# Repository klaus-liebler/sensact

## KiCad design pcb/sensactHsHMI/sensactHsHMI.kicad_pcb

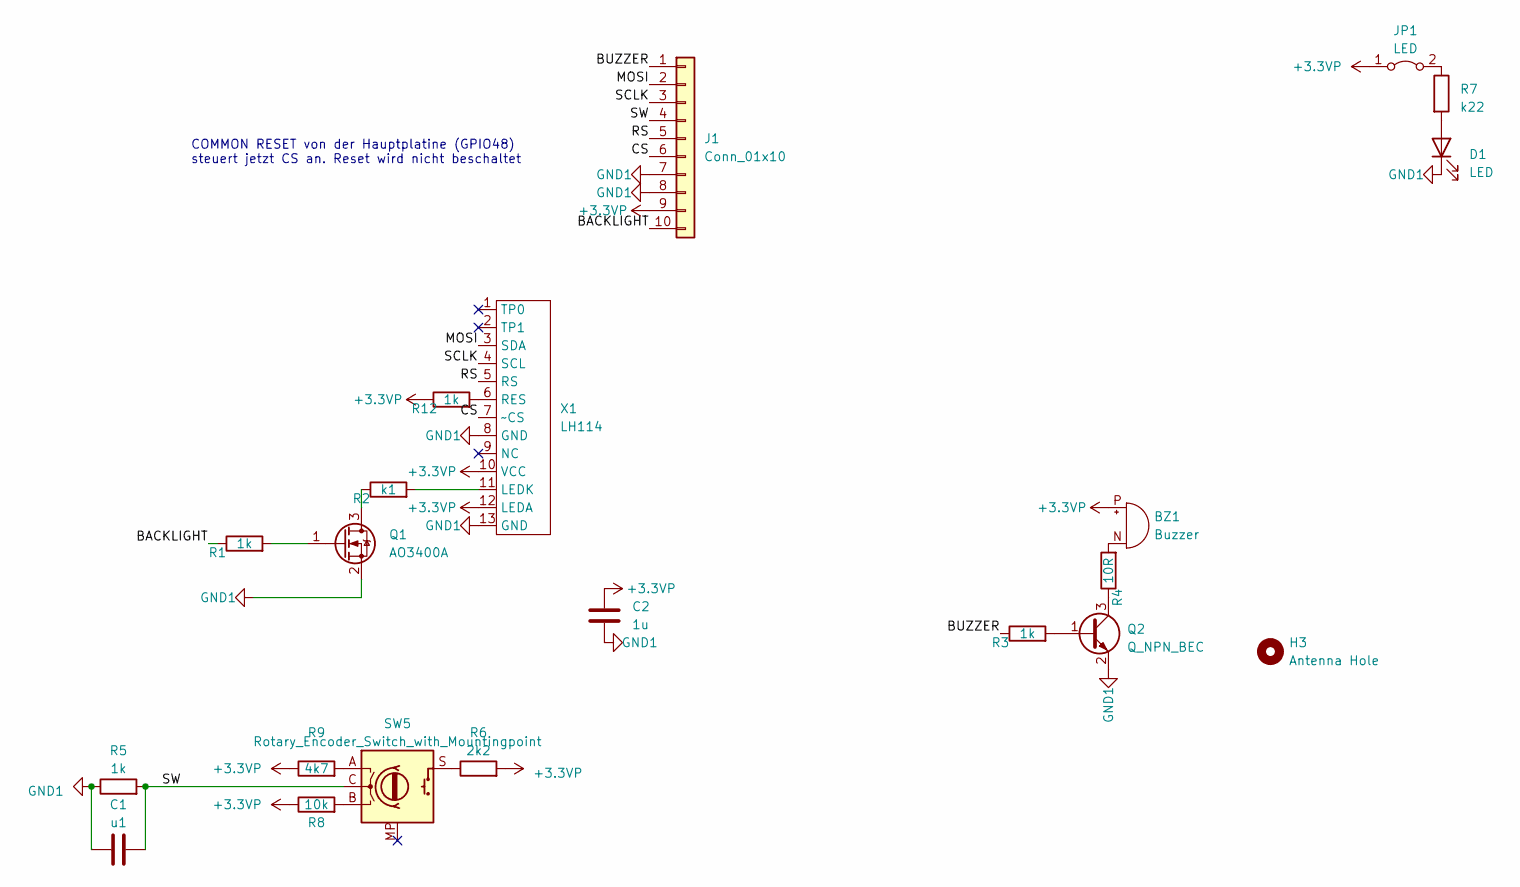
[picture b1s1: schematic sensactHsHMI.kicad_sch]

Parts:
BZ1: Buzzer; XDCR_CMT-7525-80-SMT-TR_handsolder
C1: u1; C_0805_2012Metric_Pad1.18x1.45mm_HandSolder
C2: 1u; C_0805_2012Metric_Pad1.18x1.45mm_HandSolder
D1: LED; LED_PLCC_2835_Handsoldering
H3: Antenna Hole; SMA_Schraubbefestigung
J1: Conn_01x10; FFC_FPC_10_P0.50mm_Horizontal
JP1: LED; SolderJumper-2_P1.3mm_Bridged_RoundedPad1.0x1.5mm
Q1: AO3400A; SOT-23_Handsoldering
Q2: Q_NPN_BEC; SOT-23_Handsoldering
R1, R3, R5, R12: 1k; R_0805_2012Metric_Pad1.20x1.40mm_HandSolder
R2: k1; R_0805_2012Metric_Pad1.20x1.40mm_HandSolder
R4: 10R; R_0805_2012Metric_Pad1.20x1.40mm_HandSolder
R6: 2k2; R_0805_2012Metric_Pad1.20x1.40mm_HandSolder
R7: k22; R_1206_3216Metric_Pad1.30x1.75mm_HandSolder
R8: 10k; R_0805_2012Metric_Pad1.20x1.40mm_HandSolder
R9: 4k7; R_0805_2012Metric_Pad1.20x1.40mm_HandSolder
SW5: Rotary_Encoder_Switch_with_Mountingpoint; Mitsumi_SIQ-02FVS3
X1: LH114; FP-114 13pol top only

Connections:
+3.3VP: BZ1.P (-), C2.1, J1.9, JP1.1 (A), R6.2, R8.1, R9.1, R12.1, X1.10 (VCC), X1.12 (LEDA)
/BACKLIGHT: J1.10, R1.1
/BUZZER: J1.1, R3.1
/CS: J1.6, X1.7 (~CS)
/MOSI: J1.2, X1.3 (SDA)
/RS: J1.5, X1.5 (RS)
/SCLK: J1.3, X1.4 (SCL)
/SW: C1.2, J1.4, R5.2, SW5.C
GND1: C1.1, C2.2, D1.1 (K), J1.7, J1.8, Q1.2 (S), Q2.2 (E), R5.1, X1.8 (GND), X1.13 (GND)
unnamed: BZ1.N (+), R4.2
unnamed: D1.2 (A), R7.2
unnamed: JP1.2 (B), R7.1
unnamed: Q1.3 (D), R2.1
unnamed: Q1.1 (G), R1.2
unnamed: Q2.1 (B), R3.2
unnamed: Q2.3 (C), R4.1
unnamed: R6.1, SW5.S
unnamed: R8.2, SW5.B
unnamed: R9.2, SW5.A
unnamed: R2.2, X1.11 (LEDK)
unnamed: R12.2, X1.6 (RES)

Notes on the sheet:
COMMON RESET von der Hauptplatine (GPIO48) steuert jetzt CS an. Reset wird nicht beschaltet

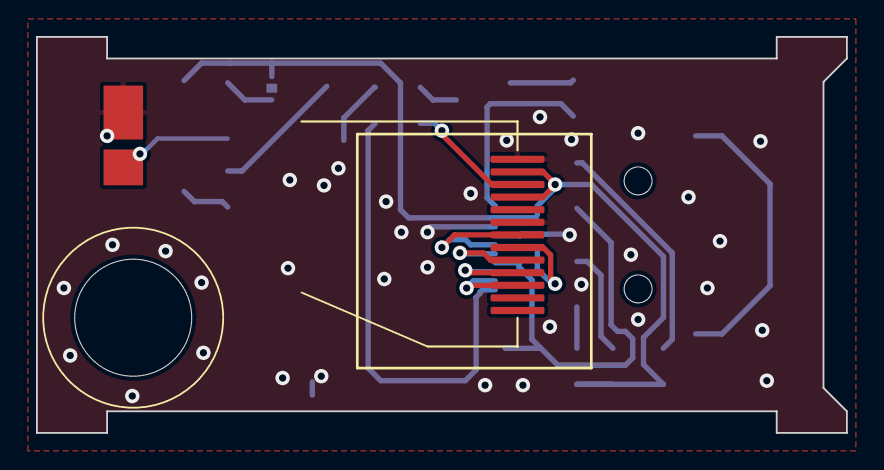
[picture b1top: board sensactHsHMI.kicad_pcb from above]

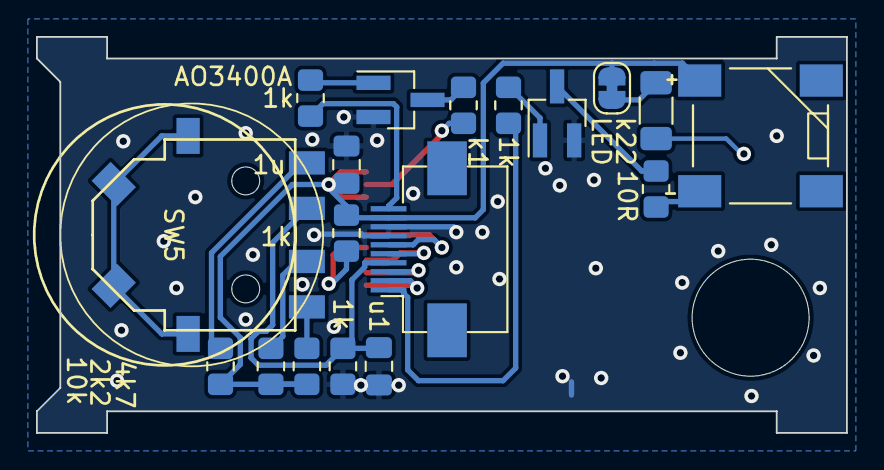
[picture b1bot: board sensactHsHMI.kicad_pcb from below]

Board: 2 copper layers, 45.0 x 22.0 mm, 21 parts (18 on the bottom side), 21 nets.

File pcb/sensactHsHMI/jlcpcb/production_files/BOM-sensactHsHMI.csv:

Comment,Designator,Footprint,LCSC
LH114,X1,FP-114 13pol top only,
u1,C1,C_0805_2012Metric_Pad1.18x1.45mm_HandSolder,
10R,R4,R_0805_2012Metric_Pad1.20x1.40mm_HandSolder,
1k,R3,R_0805_2012Metric_Pad1.20x1.40mm_HandSolder,
2k2,R6,R_0805_2012Metric_Pad1.20x1.40mm_HandSolder,
Buzzer,BZ1,XDCR_CMT-7525-80-SMT-TR_handsolder,
k1,R2,R_0805_2012Metric_Pad1.20x1.40mm_HandSolder,
1k,R1,R_0805_2012Metric_Pad1.20x1.40mm_HandSolder,
Conn_01x10,J1,FFC_FPC_10_P0.50mm_Horizontal,
Q_NPN_BEC,Q2,SOT-23_Handsoldering,
10k,R8,R_0805_2012Metric_Pad1.20x1.40mm_HandSolder,
1k,R5,R_0805_2012Metric_Pad1.20x1.40mm_HandSolder,
k22,R7,R_1206_3216Metric_Pad1.30x1.75mm_HandSolder,
LED,D1,LED_PLCC_2835_Handsoldering,
Antenna Hole,H3,SMA_Schraubbefestigung,
1u,C2,C_0805_2012Metric_Pad1.18x1.45mm_HandSolder,
1k,R12,R_0805_2012Metric_Pad1.20x1.40mm_HandSolder,
4k7,R9,R_0805_2012Metric_Pad1.20x1.40mm_HandSolder,
Rotary_Encoder_Switch_with_Mountingpoint,SW5,Mitsumi_SIQ-02FVS3,
LED,JP1,SolderJumper-2_P1.3mm_Bridged_RoundedPad1.0x1.5mm,

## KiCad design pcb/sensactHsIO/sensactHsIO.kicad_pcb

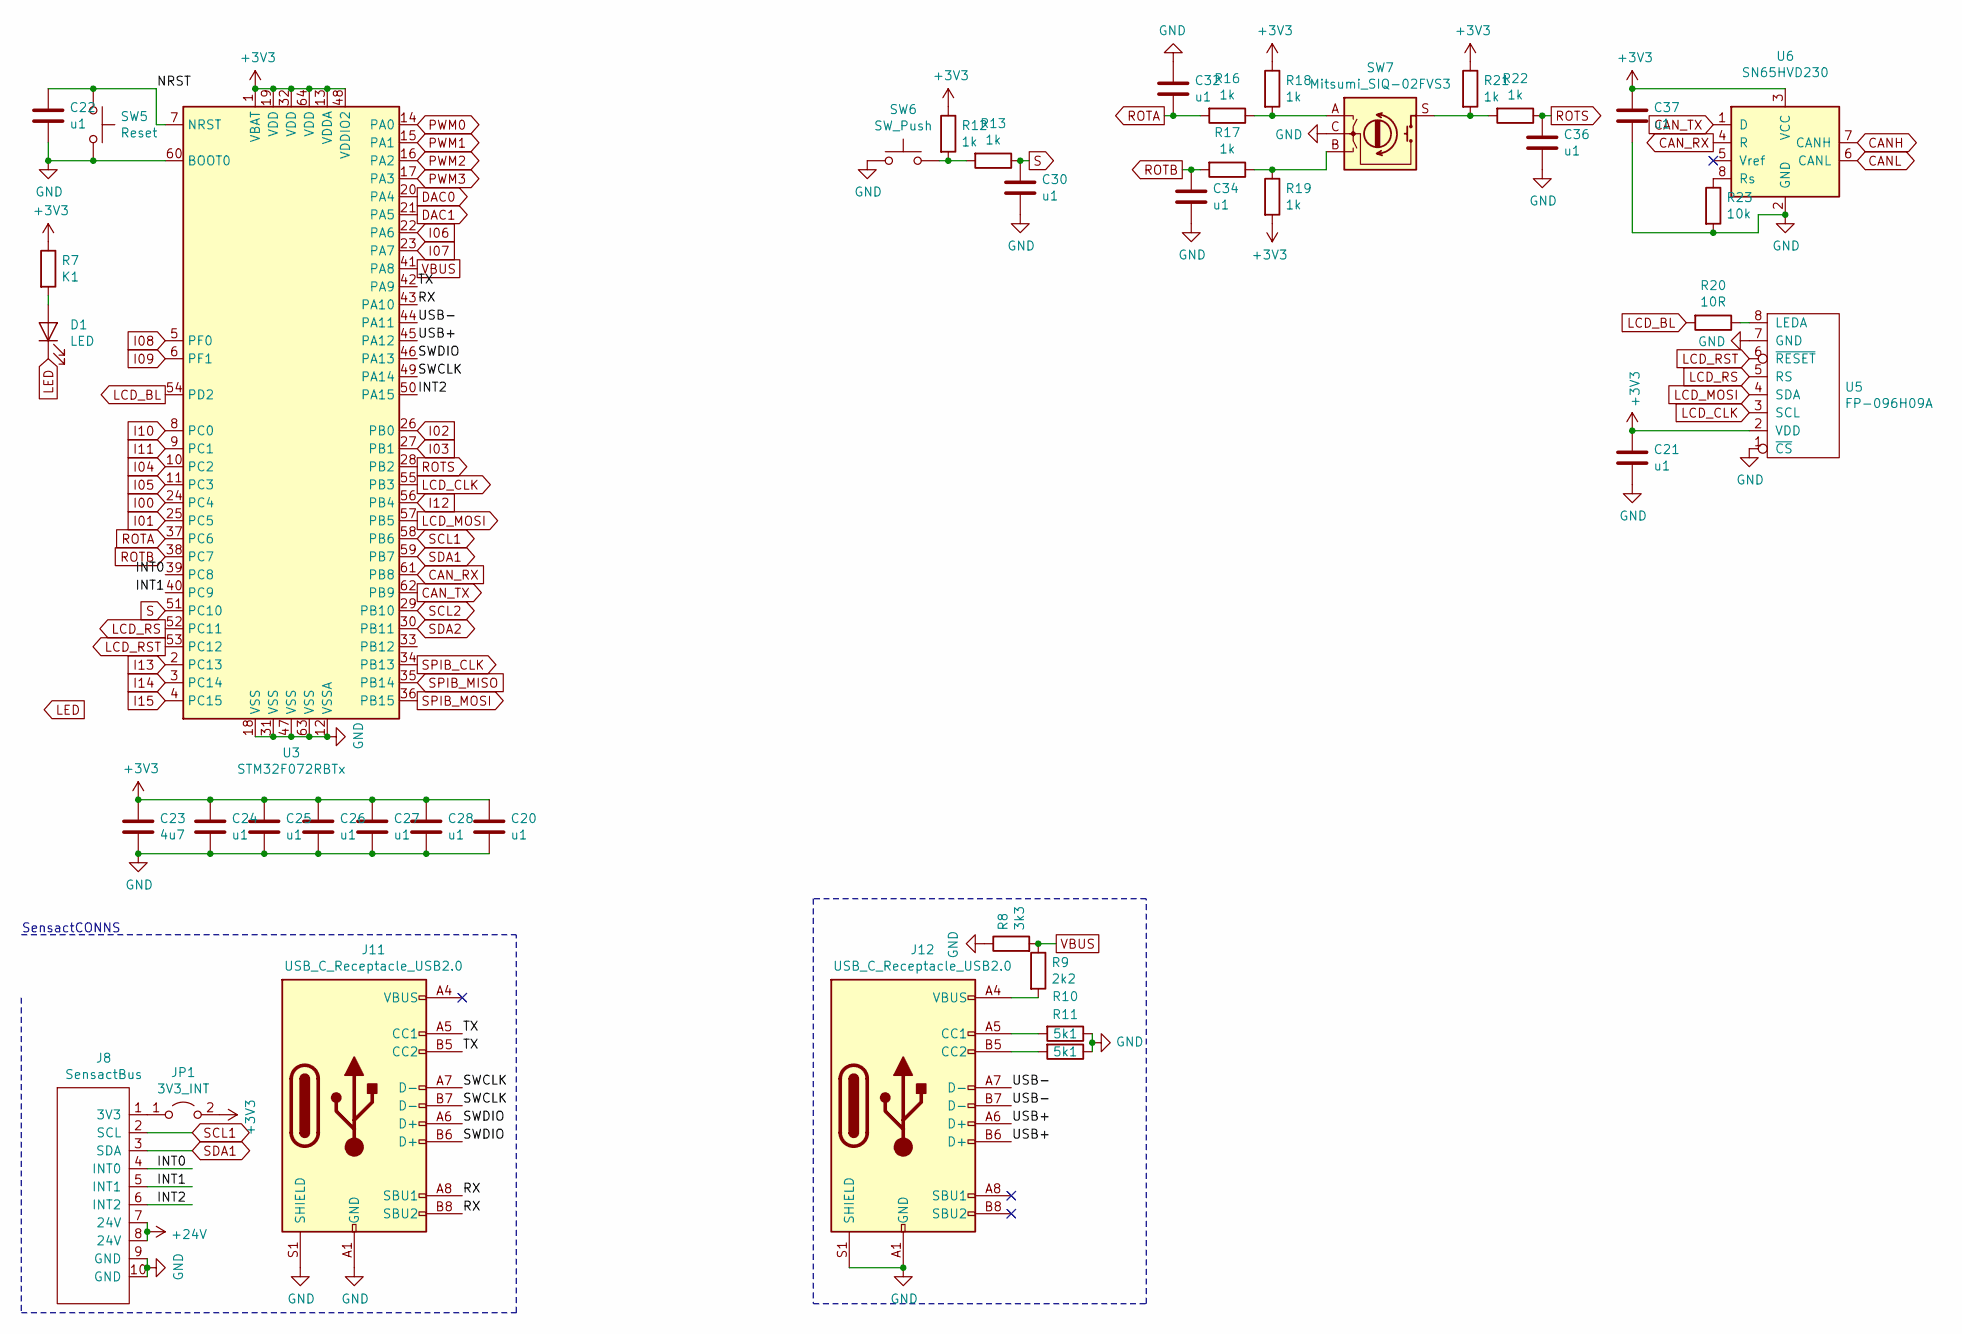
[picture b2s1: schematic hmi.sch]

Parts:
C20, C21, C22, C24, C25, C26, C27, C28, C30, C32, C34, C36, C37: u1; C_0805_2012Metric_Pad1.15x1.40mm_HandSolder
C23: 4u7; C_1206_3216Metric_Pad1.42x1.75mm_HandSolder
D1: LED; LED_0805_2012Metric_Pad1.15x1.40mm_HandSolder
J8: SensactBus; IDC-Header_2x05_P2.54mm_Horizontal
J11, J12: USB_C_Receptacle_USB2.0; USB_C_Receptacle_HRO_TYPE-C-31-M-12
JP1: 3V3_INT; SolderJumper-2_P1.3mm_Open_Pad1.0x1.5mm
R7: K1; R_0805_2012Metric_Pad1.15x1.40mm_HandSolder
R8: 3k3; R_0805_2012Metric_Pad1.15x1.40mm_HandSolder
R9: 2k2; R_0805_2012Metric_Pad1.15x1.40mm_HandSolder
R10, R11: 5k1; R_0805_2012Metric_Pad1.15x1.40mm_HandSolder
R12, R13, R16, R17, R18, R19, R21, R22: 1k; R_0805_2012Metric_Pad1.15x1.40mm_HandSolder
R20: 10R; R_0805_2012Metric_Pad1.15x1.40mm_HandSolder
R23: 10k; R_0805_2012Metric_Pad1.15x1.40mm_HandSolder
SW5: Reset; SW_SPST_2x4x3,5
SW6: SW_Push; SW_Tactile_SPST_Angled_PTS645Vx83-2LFS
SW7: Mitsumi_SIQ-02FVS3
U3: STM32F072RBTx; LQFP-64_10x10mm_P0.5mm_handsolder
U5: FP-096H09A; FPC_TOP_1x08-1MP_P0.50mm_Horizontal
U6: SN65HVD230; SOIC-8_3.9x4.9mm_Pitch1.27mm_handsolder

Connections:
+3V3: C20.1, C21.1, C23.1, C24.1, C25.1, C26.1, C27.1, C28.1, C37.1, JP1.2 (B), R7.1, R12.1, R18.1, R19.2, R21.1, U3.1 (VBAT), U3.13 (VDDA), U3.19 (VDD), U3.32 (VDD), U3.48 (VDDIO2), U3.64 (VDD), U5.2 (VDD), U6.3 (VCC); also elsewhere on the board
+24V: J8.7 (24V), J8.8 (24V); also elsewhere on the board
/hmi/INT0: J8.4 (INT0), U3.39 (PC8)
/hmi/INT1: J8.5 (INT1), U3.40 (PC9)
/hmi/INT2: J8.6 (INT2), U3.50 (PA15)
/hmi/NRST: C22.1, SW5.1, U3.7 (NRST)
/hmi/RX: J11.A8 (SBU1), J11.B8 (SBU2), U3.43 (PA10)
/hmi/SWCLK: J11.A7 (D-), J11.B7 (D-), U3.49 (PA14)
/hmi/SWDIO: J11.A6 (D+), J11.B6 (D+), U3.46 (PA13)
/hmi/TX: J11.A5 (CC1), J11.B5 (CC2), U3.42 (PA9)
/hmi/USB+: J12.A6 (D+), J12.B6 (D+), U3.45 (PA12)
/hmi/USB-: J12.A7 (D-), J12.B7 (D-), U3.44 (PA11)
CANH: U6.7 (CANH); also elsewhere on the board
CANL: U6.6 (CANL); also elsewhere on the board
CAN_RX: U3.61 (PB8), U6.4 (R)
CAN_TX: U3.62 (PB9), U6.1 (D)
DAC0: U3.20 (PA4); also elsewhere on the board
DAC1: U3.21 (PA5); also elsewhere on the board
GND: C20.2, C21.2, C22.2, C23.2, C24.2, C25.2, C26.2, C27.2, C28.2, C30.2, C32.1, C34.2, C36.2, C37.2, J8.9 (GND), J8.10 (GND), J11.A1 (GND), J11.A12 (GND), J11.B1 (GND), J11.B12 (GND), J11.S1 (SHIELD), J12.A1 (GND), J12.A12 (GND), J12.B1 (GND), J12.B12 (GND), J12.S1 (SHIELD), R8.1, R10.1, R11.1, R23.2, SW5.2, SW6.1, SW7.C, U3.12 (VSSA), U3.18 (VSS), U3.31 (VSS), U3.47 (VSS), U3.60 (BOOT0), U3.63 (VSS), U5.1 (~CS), U5.7 (GND), U6.2 (GND); also elsewhere on the board
I00: U3.24 (PC4); also elsewhere on the board
I01: U3.25 (PC5); also elsewhere on the board
I02: U3.26 (PB0); also elsewhere on the board
I03: U3.27 (PB1); also elsewhere on the board
I04: U3.10 (PC2); also elsewhere on the board
I05: U3.11 (PC3); also elsewhere on the board
I06: U3.22 (PA6); also elsewhere on the board
I07: U3.23 (PA7); also elsewhere on the board
I08: U3.5 (PF0); also elsewhere on the board
I09: U3.6 (PF1); also elsewhere on the board
I10: U3.8 (PC0); also elsewhere on the board
I11: U3.9 (PC1); also elsewhere on the board
I12: U3.56 (PB4); also elsewhere on the board
I13: U3.2 (PC13); also elsewhere on the board
I14: U3.3 (PC14); also elsewhere on the board
I15: U3.4 (PC15); also elsewhere on the board
LCD_BL: R20.2, U3.54 (PD2)
LCD_CLK: U3.55 (PB3), U5.3 (SCL)
LCD_MOSI: U3.57 (PB5), U5.4 (SDA)
LCD_RS: U3.52 (PC11), U5.5 (RS)
LCD_RST: U3.53 (PC12), U5.6 (~RESET)
unnamed: D1.2 (A), R7.2
unnamed: J8.1 (3V3), JP1.1 (A)
unnamed: J11.A4 (VBUS), J11.A9 (VBUS), J11.B4 (VBUS), J11.B9 (VBUS)
unnamed: J12.A4 (VBUS), J12.A9 (VBUS), J12.B4 (VBUS), J12.B9 (VBUS), R9.2
unnamed: J12.A5 (CC1), R10.2
unnamed: J12.B5 (CC2), R11.2
unnamed: R12.2, R13.2, SW6.2
unnamed: R16.1, R18.2, SW7.A
unnamed: R17.1, R19.1, SW7.B
unnamed: R20.1, U5.8 (LEDA)
unnamed: R21.2, R22.2, SW7.S
unnamed: R23.1, U6.8 (Rs)
PWM0: U3.14 (PA0); also elsewhere on the board
PWM1: U3.15 (PA1); also elsewhere on the board
PWM2: U3.16 (PA2); also elsewhere on the board
PWM3: U3.17 (PA3); also elsewhere on the board
ROTA: C32.2, R16.2, U3.37 (PC6)
ROTB: C34.1, R17.2, U3.38 (PC7)
ROTS: C36.1, R22.1, U3.28 (PB2)
S: C30.1, R13.1, U3.51 (PC10)
SCL1: J8.2 (SCL), U3.58 (PB6)
SCL2: U3.29 (PB10); also elsewhere on the board
SDA1: J8.3 (SDA), U3.59 (PB7)
SDA2: U3.30 (PB11); also elsewhere on the board
SPIB_CLK: U3.34 (PB13); also elsewhere on the board
SPIB_MISO: U3.35 (PB14); also elsewhere on the board
SPIB_MOSI: U3.36 (PB15); also elsewhere on the board
VBUS: R8.2, R9.1, U3.41 (PA8)

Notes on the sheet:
SensactCONNS

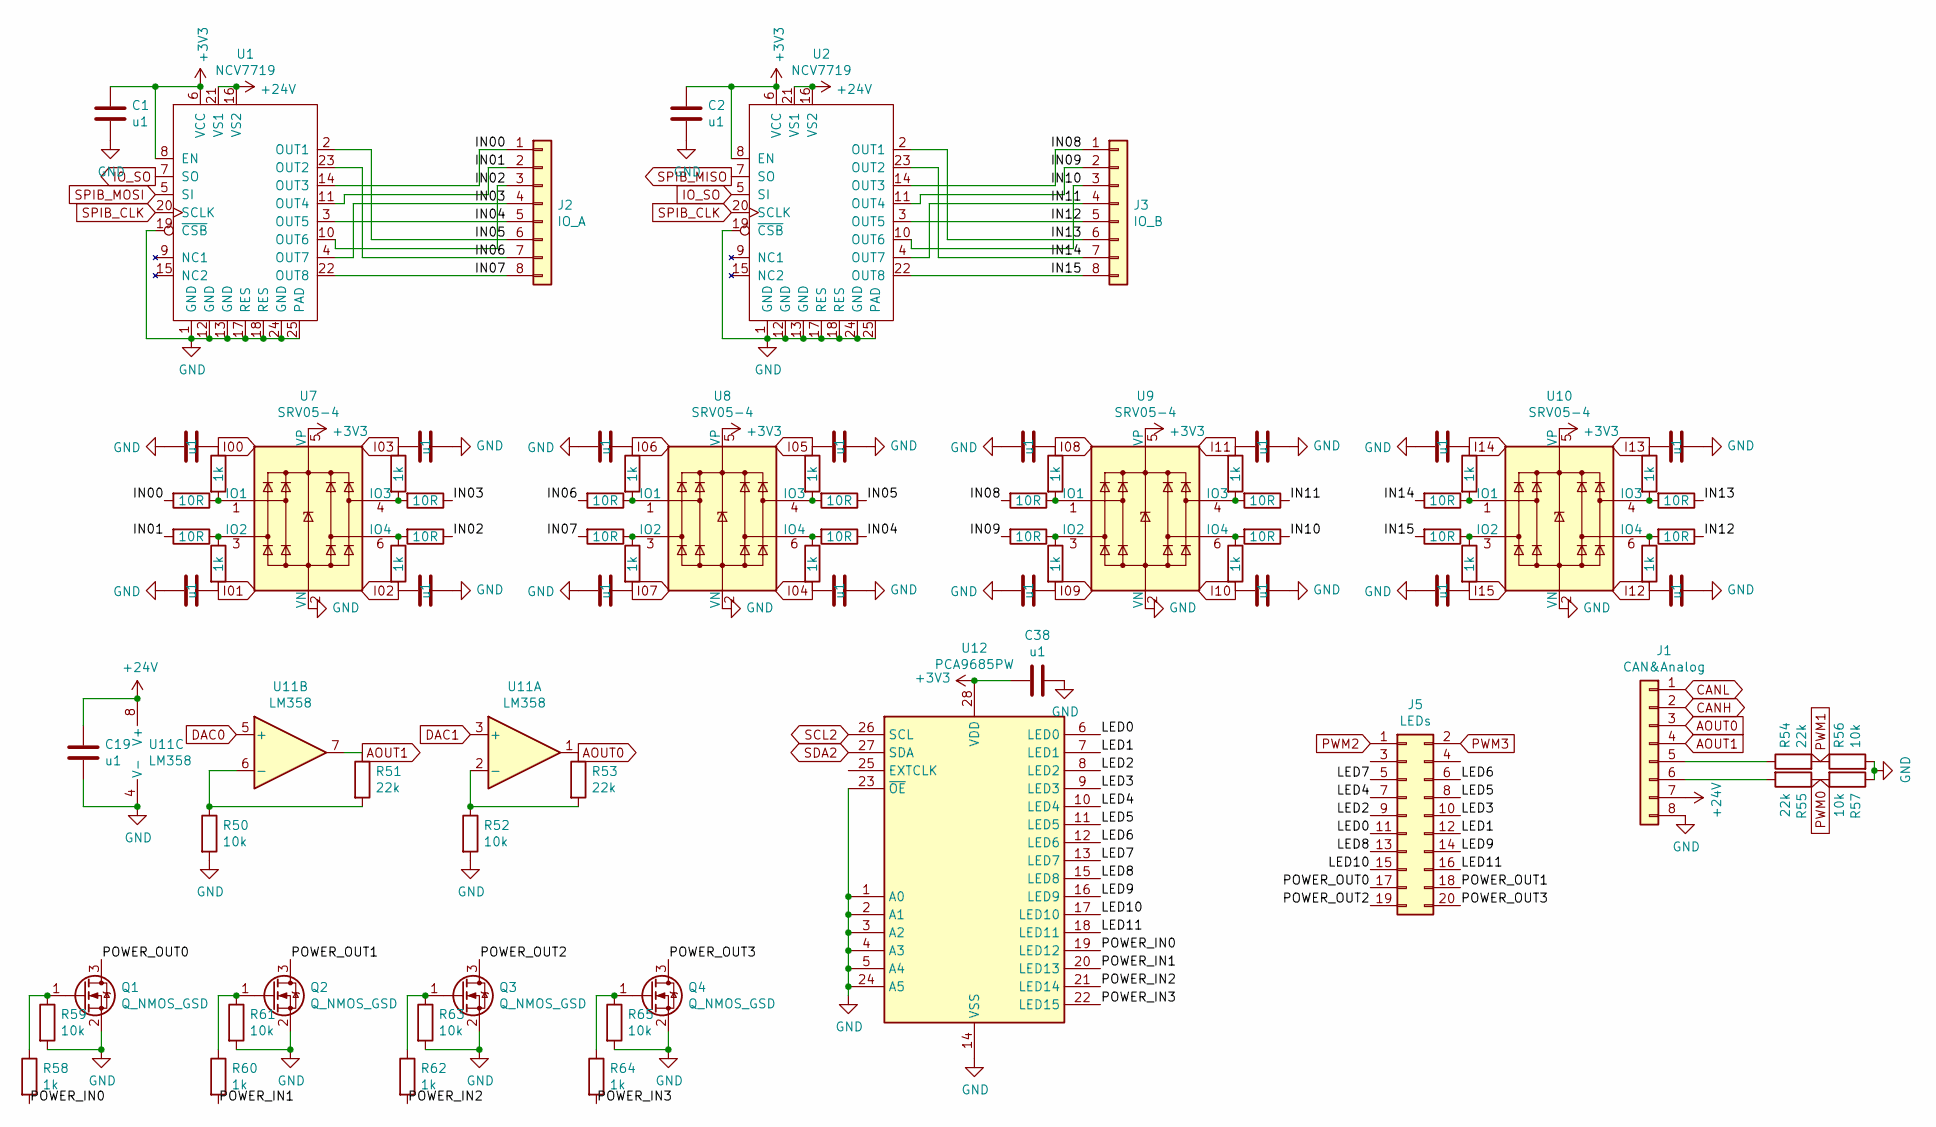
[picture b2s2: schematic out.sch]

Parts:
C1, C2, C3, C4, C5, C6, C7, C8, C9, C10, C11, C12, C13, C14, C15, C16, C17, C18, C19, C38: u1; C_0805_2012Metric_Pad1.15x1.40mm_HandSolder
J1: CAN&Analog; PhoenixContact_MC_0,5_8-G-2.5_1x08_P2.50mm_Horizontal
J2: IO_A; PhoenixContact_MC_0,5_8-G-2.5_1x08_P2.50mm_Horizontal
J3: IO_B; PhoenixContact_MC_0,5_8-G-2.5_1x08_P2.50mm_Horizontal
J5: LEDs; IDC-Header_2x10_P2.54mm_Vertical
Q1, Q2, Q3, Q4: Q_NMOS_GSD; SOT-23_Handsoldering
R1, R2, R24, R25, R26, R27, R32, R33, R34, R35, R40, R41, R42, R43, R48, R49: 10R; R_0805_2012Metric_Pad1.15x1.40mm_HandSolder
R3, R4, R5, R6, R28, R29, R30, R31, R36, R37, R38, R39, R44, R45, R46, R47, R58, R60, R62, R64: 1k; R_0805_2012Metric_Pad1.15x1.40mm_HandSolder
R50, R52, R56, R57, R59, R61, R63, R65: 10k; R_0805_2012Metric_Pad1.15x1.40mm_HandSolder
R51, R53, R54, R55: 22k; R_0805_2012Metric_Pad1.15x1.40mm_HandSolder
U1, U2: NCV7719; SSOP-24_3.9x8.7mm_P0.65mm_EP2.7x5.6mm
U7, U8, U9, U10: SRV05-4; SOT-23-6_handsolder
U11: LM358
U12: PCA9685PW; TSSOP-28_4.4x9.7mm_Pitch0.65mm_handsolder

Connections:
+3V3: C1.1, C2.1, C38.2, U1.6 (VCC), U1.8 (EN), U2.6 (VCC), U2.8 (EN), U7.5 (VP), U8.5 (VP), U9.5 (VP), U10.5 (VP), U12.28 (VDD); also elsewhere on the board
+24V: C19.1, J1.7, U1.16 (VS2), U1.21 (VS1), U2.16 (VS2), U2.21 (VS1), U11.8 (V+); also elsewhere on the board
/out/IN00: J2.1, R1.2, U1.14 (OUT3)
/out/IN01: J2.2, R2.2, U1.11 (OUT4)
/out/IN02: J2.3, R25.1, U1.10 (OUT6)
/out/IN03: J2.4, R24.1, U1.4 (OUT7)
/out/IN04: J2.5, R33.1, U1.3 (OUT5)
/out/IN05: J2.6, R32.1, U1.2 (OUT1)
/out/IN06: J2.7, R26.2, U1.23 (OUT2)
/out/IN07: J2.8, R27.2, U1.22 (OUT8)
/out/IN08: J3.1, R34.2, U2.14 (OUT3)
/out/IN09: J3.2, R35.2, U2.11 (OUT4)
/out/IN10: J3.3, R41.1, U2.10 (OUT6)
/out/IN11: J3.4, R40.1, U2.4 (OUT7)
/out/IN12: J3.5, R49.1, U2.3 (OUT5)
/out/IN13: J3.6, R48.1, U2.2 (OUT1)
/out/IN14: J3.7, R42.2, U2.23 (OUT2)
/out/IN15: J3.8, R43.2, U2.22 (OUT8)
/out/LED0: J5.11, U12.6 (LED0)
/out/LED1: J5.12, U12.7 (LED1)
/out/LED2: J5.9, U12.8 (LED2)
/out/LED3: J5.10, U12.9 (LED3)
/out/LED4: J5.7, U12.10 (LED4)
/out/LED5: J5.8, U12.11 (LED5)
/out/LED6: J5.6, U12.12 (LED6)
/out/LED7: J5.5, U12.13 (LED7)
/out/LED8: J5.13, U12.15 (LED8)
/out/LED9: J5.14, U12.16 (LED9)
/out/LED10: J5.15, U12.17 (LED10)
/out/LED11: J5.16, U12.18 (LED11)
/out/POWER_IN0: R58.2, U12.19 (LED12)
/out/POWER_IN1: R60.2, U12.20 (LED13)
/out/POWER_IN2: R62.2, U12.21 (LED14)
/out/POWER_IN3: R64.2, U12.22 (LED15)
/out/POWER_OUT0: J5.17, Q1.3 (D)
/out/POWER_OUT1: J5.18, Q2.3 (D)
/out/POWER_OUT2: J5.19, Q3.3 (D)
/out/POWER_OUT3: J5.20, Q4.3 (D)
AOUT0: J1.3, R53.1, U11.1
AOUT1: J1.4, R51.1, U11.7
CANH: J1.2; also elsewhere on the board
CANL: J1.1; also elsewhere on the board
DAC0: U11.5 (+); also elsewhere on the board
DAC1: U11.3 (+); also elsewhere on the board
GND: C1.2, C2.2, C3.2, C4.2, C5.1, C6.1, C7.2, C8.2, C9.1, C10.1, C11.2, C12.2, C13.1, C14.1, C15.2, C16.2, C17.1, C18.1, C19.2, C38.1, J1.8, Q1.2 (S), Q2.2 (S), Q3.2 (S), Q4.2 (S), R50.2, R52.2, R56.2, R57.1, R59.2, R61.2, R63.2, R65.2, U1.1 (GND), U1.12 (GND), U1.13 (GND), U1.17 (RES), U1.18 (RES), U1.19 (~CSB), U1.24 (GND), U1.25 (PAD), U2.1 (GND), U2.12 (GND), U2.13 (GND), U2.17 (RES), U2.18 (RES), U2.19 (~CSB), U2.24 (GND), U2.25 (PAD), U7.2 (VN), U8.2 (VN), U9.2 (VN), U10.2 (VN), U11.4 (V-), U12.1 (A0), U12.2 (A1), U12.3 (A2), U12.4 (A3), U12.5 (A4), U12.14 (VSS), U12.23 (~OE), U12.24 (A5); also elsewhere on the board
I00: C3.1, R3.1; also elsewhere on the board
I01: C4.1, R4.2; also elsewhere on the board
I02: C6.2, R6.2; also elsewhere on the board
I03: C5.2, R5.1; also elsewhere on the board
I04: C10.2, R31.2; also elsewhere on the board
I05: C9.2, R30.1; also elsewhere on the board
I06: C7.1, R28.1; also elsewhere on the board
I07: C8.1, R29.2; also elsewhere on the board
I08: C11.1, R36.1; also elsewhere on the board
I09: C12.1, R37.2; also elsewhere on the board
I10: C14.2, R39.2; also elsewhere on the board
I11: C13.2, R38.1; also elsewhere on the board
I12: C18.2, R47.2; also elsewhere on the board
I13: C17.2, R46.1; also elsewhere on the board
I14: C15.1, R44.1; also elsewhere on the board
I15: C16.1, R45.2; also elsewhere on the board
IO_SO: U1.7 (SO), U2.5 (SI)
unnamed: J1.5, R54.1
unnamed: J1.6, R55.2
unnamed: Q1.1 (G), R58.1, R59.1
unnamed: Q2.1 (G), R60.1, R61.1
unnamed: Q3.1 (G), R62.1, R63.1
unnamed: Q4.1 (G), R64.1, R65.1
unnamed: R1.1, R3.2, U7.1 (IO1)
unnamed: R2.1, R4.1, U7.3 (IO2)
unnamed: R5.2, R24.2, U7.4 (IO3)
unnamed: R6.1, R25.2, U7.6 (IO4)
unnamed: R26.1, R28.2, U8.1 (IO1)
unnamed: R27.1, R29.1, U8.3 (IO2)
unnamed: R30.2, R32.2, U8.4 (IO3)
unnamed: R31.1, R33.2, U8.6 (IO4)
unnamed: R34.1, R36.2, U9.1 (IO1)
unnamed: R35.1, R37.1, U9.3 (IO2)
unnamed: R38.2, R40.2, U9.4 (IO3)
unnamed: R39.1, R41.2, U9.6 (IO4)
unnamed: R42.1, R44.2, U10.1 (IO1)
unnamed: R43.1, R45.1, U10.3 (IO2)
unnamed: R46.2, R48.2, U10.4 (IO3)
unnamed: R47.1, R49.2, U10.6 (IO4)
unnamed: R50.1, R51.2, U11.6 (-)
unnamed: R52.1, R53.2, U11.2 (-)
PWM0: R55.1, R57.2; also elsewhere on the board
PWM1: R54.2, R56.1; also elsewhere on the board
PWM2: J5.1; also elsewhere on the board
PWM3: J5.2; also elsewhere on the board
SCL2: U12.26 (SCL); also elsewhere on the board
SDA2: U12.27 (SDA); also elsewhere on the board
SPIB_CLK: U1.20 (SCLK), U2.20 (SCLK); also elsewhere on the board
SPIB_MISO: U2.7 (SO); also elsewhere on the board
SPIB_MOSI: U1.5 (SI); also elsewhere on the board

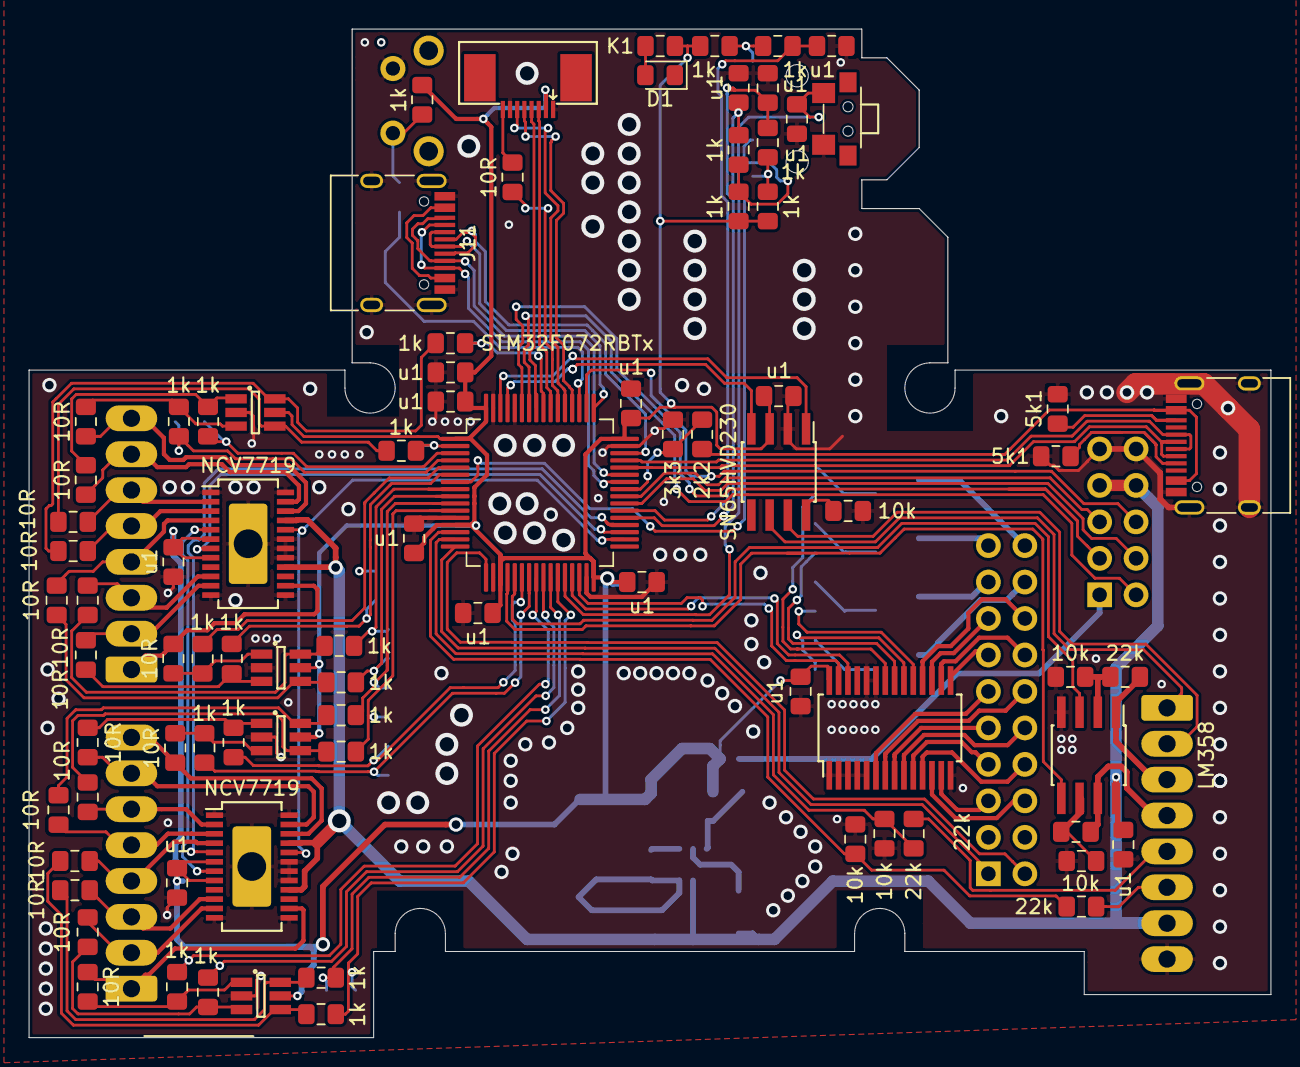
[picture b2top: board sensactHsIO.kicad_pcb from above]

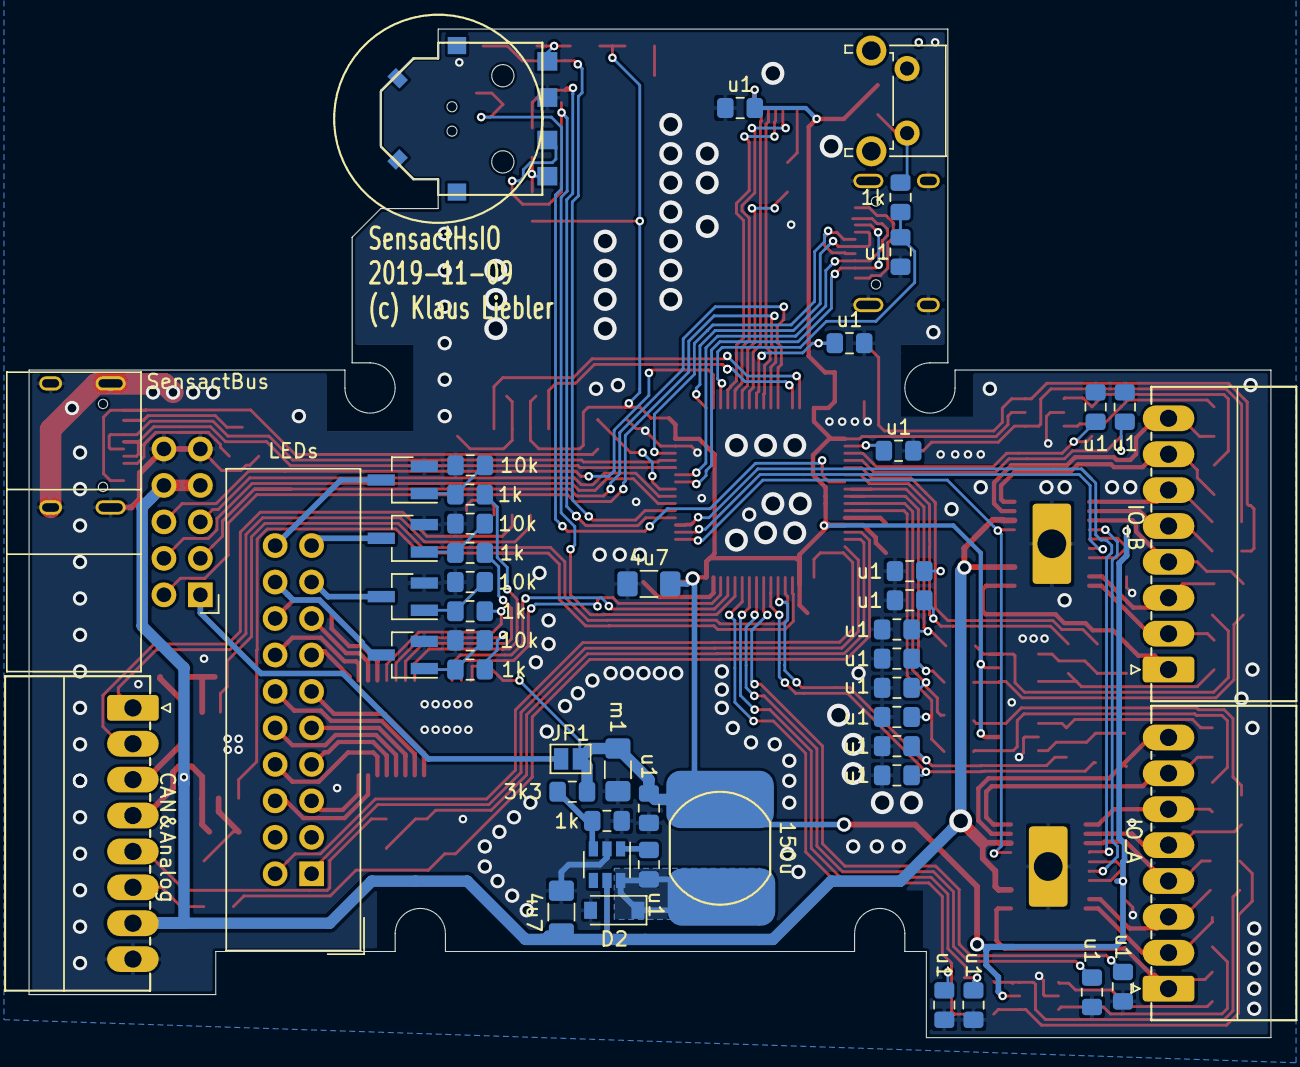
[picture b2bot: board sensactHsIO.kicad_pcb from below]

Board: 2 copper layers, 86.5 x 70.2 mm, 133 parts (49 on the bottom side), 134 nets.

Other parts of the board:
C29: 4u7; C_1206_3216Metric_Pad1.42x1.75mm_HandSolder
C31, C35: u1; C_0805_2012Metric_Pad1.15x1.40mm_HandSolder
C33: m1; C_1206_3216Metric_Pad1.42x1.75mm_HandSolder
D2: MBR0540; D_SOD-123
L5: 150u; Inductor_CD75_handsolder
R14: 3k3; R_0805_2012Metric_Pad1.15x1.40mm_HandSolder
R15: 1k; R_0805_2012Metric_Pad1.15x1.40mm_HandSolder
U4: LMR14206; SOT-23-6

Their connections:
+3V3: C33.1, C35.1, L5.1, R14.1; also elsewhere on the board
+24V: C29.1, U4.5; also elsewhere on the board
/hmi/CB: C31.2, U4.1
/hmi/FB: R14.2, R15.1, U4.3
/hmi/SW: C31.1, D2.1, L5.2, U4.6
GND: C29.2, C33.2, C35.2, D2.2, R15.2, U4.2; also elsewhere on the board
